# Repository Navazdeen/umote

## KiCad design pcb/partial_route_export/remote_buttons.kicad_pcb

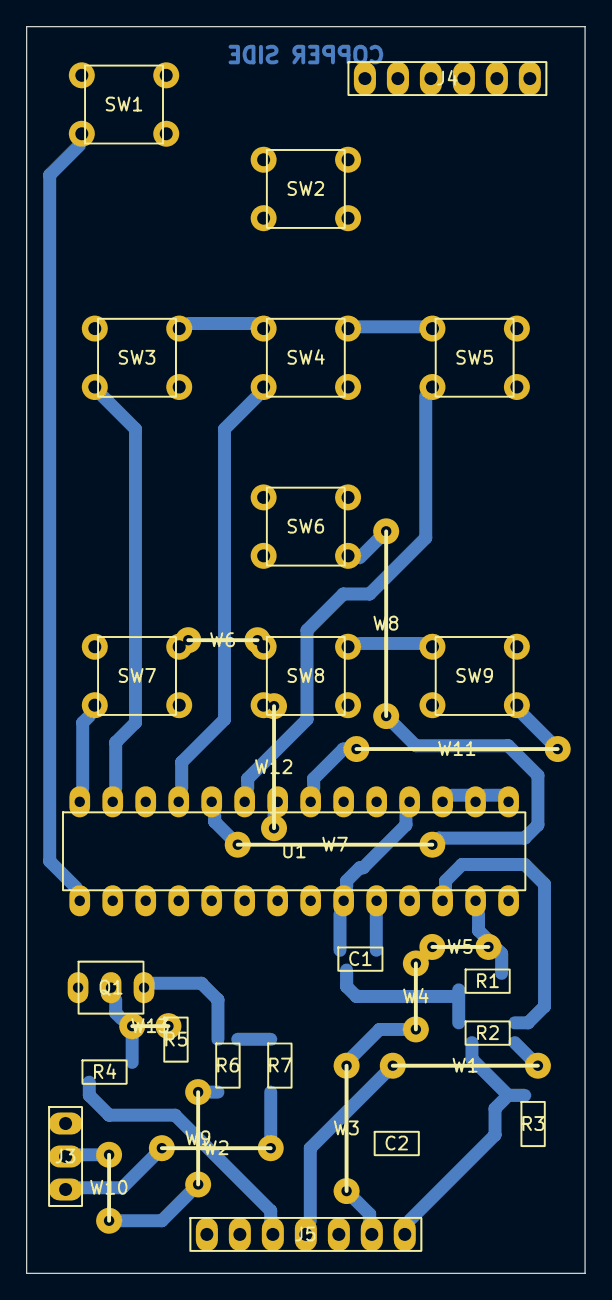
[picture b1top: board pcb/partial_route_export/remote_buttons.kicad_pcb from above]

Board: 2 copper layers, 43.0 x 96.0 mm, 36 parts (0 on the bottom side), 20 nets.

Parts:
C1: 100nF; C_1206
C2: 47uF; C_1206
J3: IR LED; HDR_1x3
J4: INMP441; HDR_1x6
J5: TO DISPLAY; HDR_1x7
Q1: S8050 EBC; TO92_wide
R1, R2: 4.7k; R_1206
R3, R5: 10k; R_1206
R4: 1k; R_1206
R6, R7: 15R; R_1206
SW1: POWER; SW_6x6
SW2: UP; SW_6x6
SW3: LEFT; SW_6x6
SW4: OK; SW_6x6
SW5: RIGHT; SW_6x6
SW6: DOWN; SW_6x6
SW7: BACK; SW_6x6
SW8: HOME; SW_6x6
SW9: VOICE; SW_6x6
U1: MCP23017; DIP28
W1, W2, W3, W4, W5, W6, W7, W8, W9, W10, W11, W12, W13: wire; WIRE_JUMPER

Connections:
3V3: C1.1, J5.7, R1.1, R2.1, R3.1, U1.9, U1.18
BTN_BACK: SW7.3, SW7.4, U1.28
BTN_DOWN: SW6.3, SW6.4, U1.24, W7.1, W7.2, W8.1, W8.2
BTN_HOME: SW8.3, SW8.4, U1.22, W12.1, W12.2
BTN_LEFT: SW3.3, SW3.4, U1.27
BTN_OK: SW4.3, SW4.4, U1.25
BTN_POWER: SW1.3, SW1.4, U1.1
BTN_RIGHT: SW5.3, SW5.4, U1.23
BTN_UP: SW2.3, SW2.4, U1.26
BTN_VOICE: SW9.3, SW9.4, U1.21, W11.1, W11.2
GND: C1.2, C2.2, J5.5, Q1.E, R5.2, SW1.1, SW1.2, SW2.1, SW2.2, SW3.1, SW3.2, SW4.1, SW4.2, SW5.1, SW5.2, SW6.1, SW6.2, SW7.1, SW7.2, SW8.1, SW8.2, SW9.1, SW9.2, U1.10, U1.15, U1.16, U1.17, W6.1, W6.2
INT: J5.2, R3.2, U1.20
IR: J5.3, R4.1
K1: J3.2, R6.2, W9.1, W9.2, W10.1, W10.2
K2: J3.3, R7.2, W2.1, W2.2
QB: Q1.B, R4.2, R5.1, W13.1, W13.2
QC: Q1.C, R6.1, R7.1
SCL: J5.4, R2.2, U1.12, W1.1, W1.2
SDA: J5.6, R1.2, U1.13, W3.1, W3.2, W4.1, W4.2, W5.1, W5.2
VBAT: C2.1, J3.1, J5.1

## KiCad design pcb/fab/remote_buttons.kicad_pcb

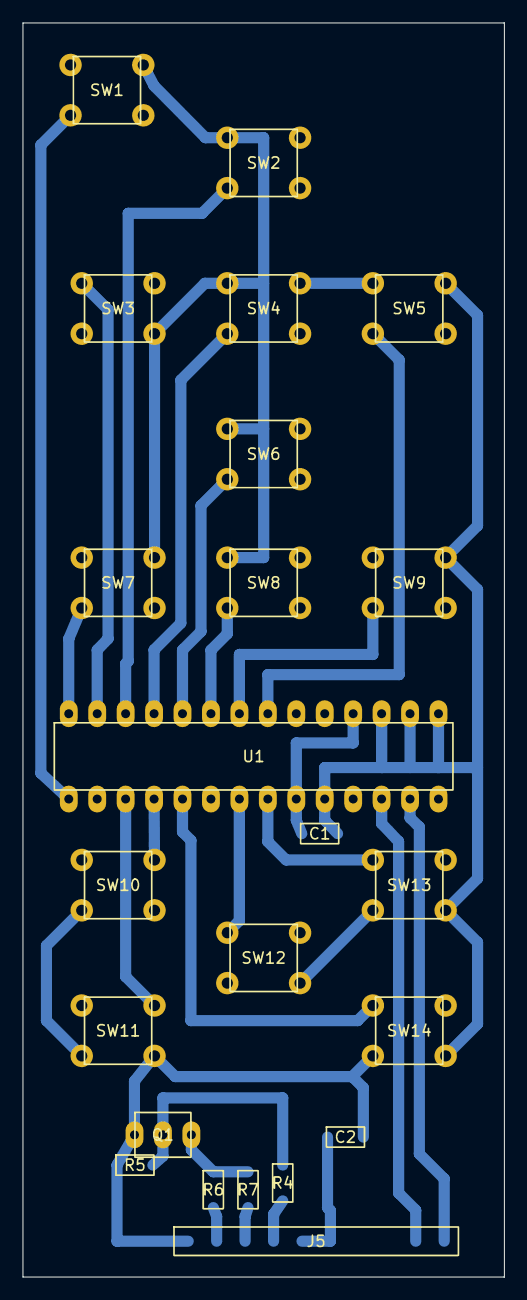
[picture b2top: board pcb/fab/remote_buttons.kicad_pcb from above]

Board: 2 copper layers, 43.0 x 112.0 mm, 23 parts (0 on the bottom side), 25 nets.

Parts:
C1: 100nF; C_1206
C2: 47uF; C_1206
J5: TO DISPLAY; HDR_1x10
Q1: S8050 EBC; TO92_wide
R4: 1k; R_1206
R5: 10k; R_1206
R6, R7: 15R; R_1206
SW1: POWER; SW_6x6
SW2: UP; SW_6x6
SW3: LEFT; SW_6x6
SW4: OK; SW_6x6
SW5: RIGHT; SW_6x6
SW6: DOWN; SW_6x6
SW7: BACK; SW_6x6
SW8: HOME; SW_6x6
SW9: VOICE; SW_6x6
SW10: VOL_UP; SW_6x6
SW11: VOL_DOWN; SW_6x6
SW12: MUTE; SW_6x6
SW13: CH_UP; SW_6x6
SW14: CH_DOWN; SW_6x6
U1: MCP23017; DIP28

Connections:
3V3: C1.1, J5.7, U1.9, U1.18
BTN_BACK: SW7.3, SW7.4, U1.28
BTN_CH_DOWN: SW14.3, SW14.4, U1.5
BTN_CH_UP: SW13.3, SW13.4, U1.8
BTN_DOWN: SW6.3, SW6.4, U1.24
BTN_HOME: SW8.3, SW8.4, U1.23
BTN_LEFT: SW3.3, SW3.4, U1.27
BTN_MUTE: SW12.3, SW12.4, U1.7
BTN_OK: SW4.3, SW4.4, U1.25
BTN_POWER: SW1.3, SW1.4, U1.1
BTN_RIGHT: SW5.3, SW5.4, U1.21
BTN_UP: SW2.3, SW2.4, U1.26
BTN_VOICE: SW9.3, SW9.4, U1.22
BTN_VOL_DOWN: SW11.3, SW11.4, U1.3
BTN_VOL_UP: SW10.3, SW10.4, U1.4
GND: C1.2, C2.2, J5.1, Q1.E, R5.1, SW1.1, SW1.2, SW2.1, SW2.2, SW3.1, SW3.2, SW4.1, SW4.2, SW5.1, SW5.2, SW6.1, SW6.2, SW7.1, SW7.2, SW8.1, SW8.2, SW9.1, SW9.2, SW10.1, SW10.2, SW11.1, SW11.2, SW12.1, SW12.2, SW13.1, SW13.2, SW14.1, SW14.2, U1.10, U1.15, U1.16, U1.17
INT: J5.8, U1.20
IR: J5.4, R4.2
K1: J5.2, R6.2
K2: J5.3, R7.2
QB: Q1.B, R4.1, R5.2
QC: Q1.C, R6.1, R7.1
SCL: J5.9, U1.12
SDA: J5.10, U1.13
VBAT: C2.1, J5.5, J5.6
